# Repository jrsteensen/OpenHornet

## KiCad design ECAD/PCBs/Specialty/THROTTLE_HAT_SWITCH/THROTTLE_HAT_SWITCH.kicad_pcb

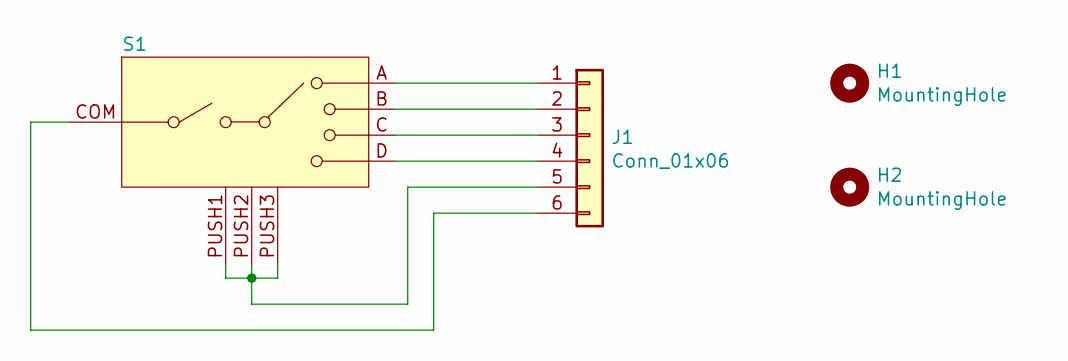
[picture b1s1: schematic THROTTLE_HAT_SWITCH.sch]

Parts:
H1, H2: MountingHole; MountingHole_3mm
J1: Conn_01x06; JST_PH_B6B-PH-K_1x06_P2.00mm_Vertical
S1: 8WayHat_CenterPush; RKJXM10

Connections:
unnamed: J1.1, S1.A
unnamed: J1.2, S1.B
unnamed: J1.3, S1.C
unnamed: J1.4, S1.D
unnamed: J1.5, S1.PUSH1, S1.PUSH2, S1.PUSH3
unnamed: J1.6, S1.COM

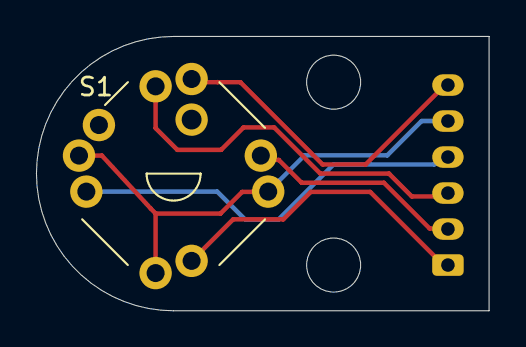
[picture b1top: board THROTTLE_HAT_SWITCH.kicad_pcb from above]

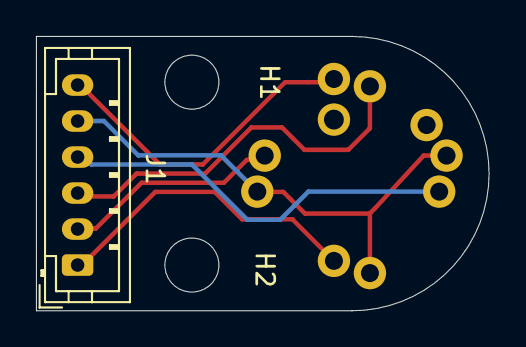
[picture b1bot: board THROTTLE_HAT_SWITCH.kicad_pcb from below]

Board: 2 copper layers, 25.1 x 15.2 mm, 4 parts (3 on the bottom side), 6 nets.

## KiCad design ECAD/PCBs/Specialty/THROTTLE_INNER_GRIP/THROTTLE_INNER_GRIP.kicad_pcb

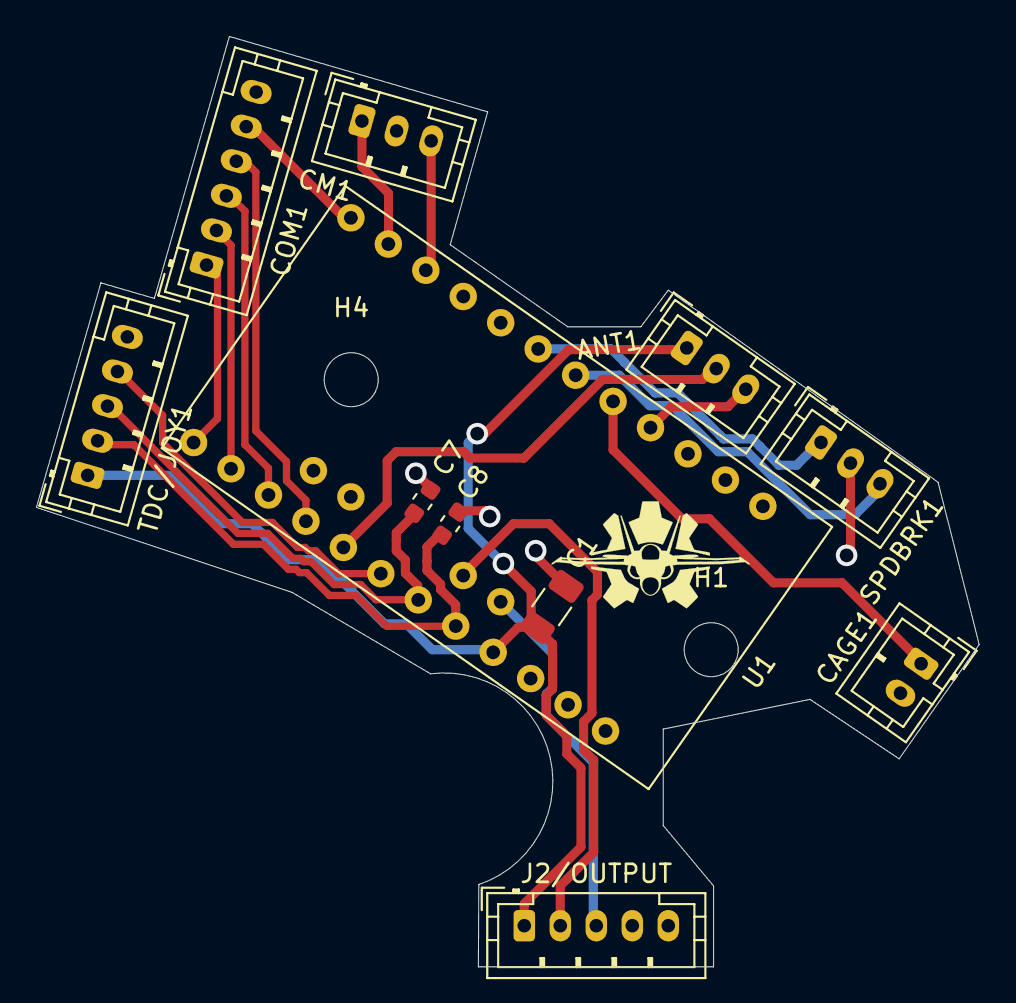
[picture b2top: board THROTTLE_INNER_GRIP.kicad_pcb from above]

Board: 2 copper layers, 52.4 x 51.7 mm, 13 parts (0 on the bottom side), 18 nets.

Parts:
ANT1: Conn_01x03; JST_PH_B3B-PH-K_1x03_P2.00mm_Vertical
C1: 10uF; C_1206_3216Metric
C7, C8: 0.1uF; C_0603_1608Metric
CAGE1: Conn_01x02; JST_PH_B2B-PH-K_1x02_P2.00mm_Vertical
CM1: Conn_01x03; JST_PH_B3B-PH-K_1x03_P2.00mm_Vertical
COM1: COMS; JST_PH_B6B-PH-K_1x06_P2.00mm_Vertical
H1, H4: MountingHole; MountingHole_3mm
J2/OUTPUT: BASE; JST_PH_B5B-PH-K_1x05_P2.00mm_Vertical
SPDBRK1: Conn_01x03; JST_PH_B3B-PH-K_1x03_P2.00mm_Vertical
TDC/JOY1: JOYSTICK; JST_PH_B5B-PH-K_1x05_P2.00mm_Vertical
U1: ProMini_NoProgrammingHeader; Arduino_Mini_Pro_No_Programming_Header

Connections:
/A: COM1.1, U1.13
/ANTENNA_ELEVATION: ANT1.2, U1.17
/B: COM1.2, U1.14
/C: COM1.3, U1.15
/CAGE-UNCAGE: CAGE1.1, U1.5
/COUNTERMEASURES_AFT: CM1.3, U1.10
/COUNTERMEASURES_FWD: CM1.1, U1.11
/D: COM1.4, U1.16
/I2C_DATA: J2/OUTPUT.2, U1.33
/I2C_SCK: J2/OUTPUT.3, U1.34
/JOY_SW: TDC/JOY1.4, U1.18
/JOY_X: C8.1, TDC/JOY1.2, U1.20
/JOY_Y: C7.1, TDC/JOY1.3, U1.19
/PUSH: COM1.5, U1.12
/SPEEDBREAK_EXTEND: SPDBRK1.1, U1.7
/SPEEDBREAK_RETRACT: SPDBRK1.3, U1.6
GND: ANT1.3, C1.2, C7.2, C8.2, CAGE1.2, CM1.2, COM1.6, J2/OUTPUT.5, SPDBRK1.2, TDC/JOY1.5, U1.4, U1.23
VCC: ANT1.1, C1.1, J2/OUTPUT.1, TDC/JOY1.1, U1.21

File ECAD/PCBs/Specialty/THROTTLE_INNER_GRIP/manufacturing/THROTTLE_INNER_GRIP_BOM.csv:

Comment,Designator,Footprint,LCSC
Conn_01x03,"ANT1,CM1,SP1",Connector_JST:JST_PH_B3B-PH-K_1x03_P2.00mm_Vertical,
10uF,C1,Capacitor_SMD:C_1206_3216Metric,C13585
0.1uF,"C7,C8",Capacitor_SMD:C_0603_1608Metric,C14663
Conn_01x02,CAGE1,Connector_JST:JST_PH_B2B-PH-K_1x02_P2.00mm_Vertical,
COMS,COM1,Connector_JST:JST_PH_B6B-PH-K_1x06_P2.00mm_Vertical,
MountingHole,"H1,H4",MountingHole:MountingHole_3mm,
BASE,J2,Connector_JST:JST_PH_B5B-PH-K_1x05_P2.00mm_Vertical,
JOYSTICK,JOY1,Connector_JST:JST_PH_B5B-PH-K_1x05_P2.00mm_Vertical,
ProMini_NoProgrammingHeader,U1,KiCAD_Libraries:Arduino_Mini_Pro_No_Programming_Header,

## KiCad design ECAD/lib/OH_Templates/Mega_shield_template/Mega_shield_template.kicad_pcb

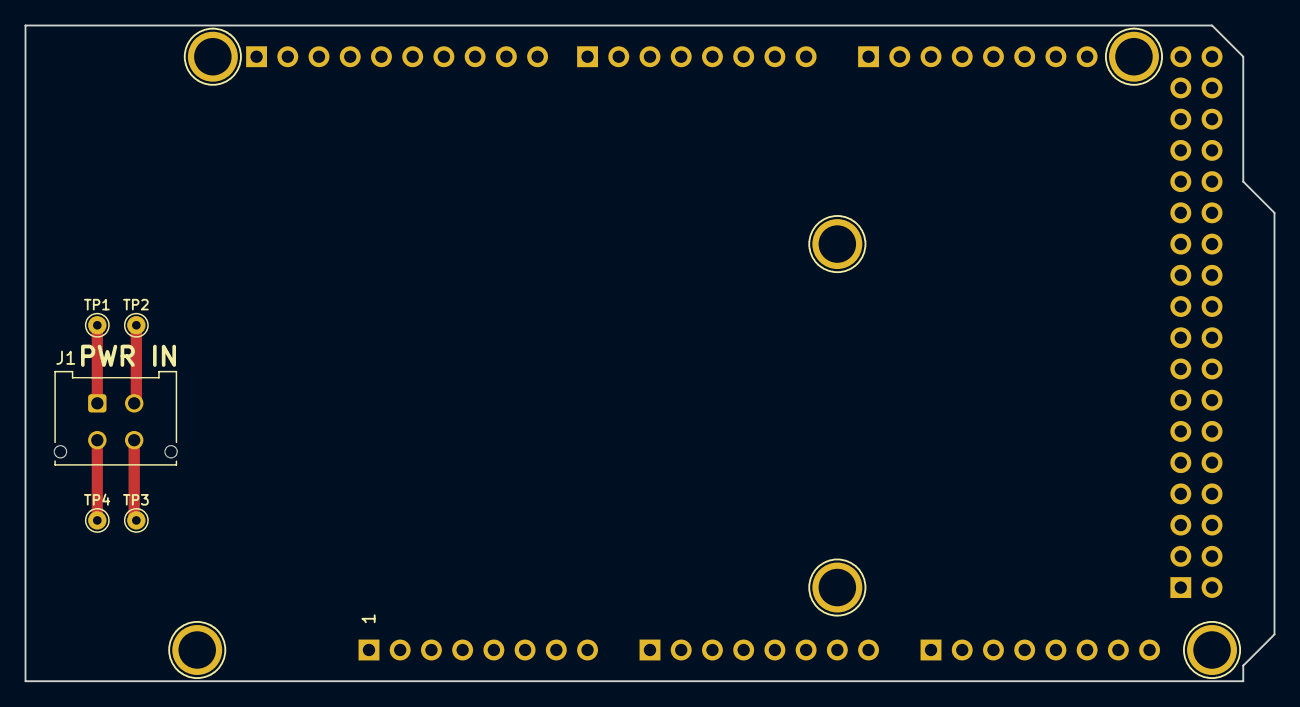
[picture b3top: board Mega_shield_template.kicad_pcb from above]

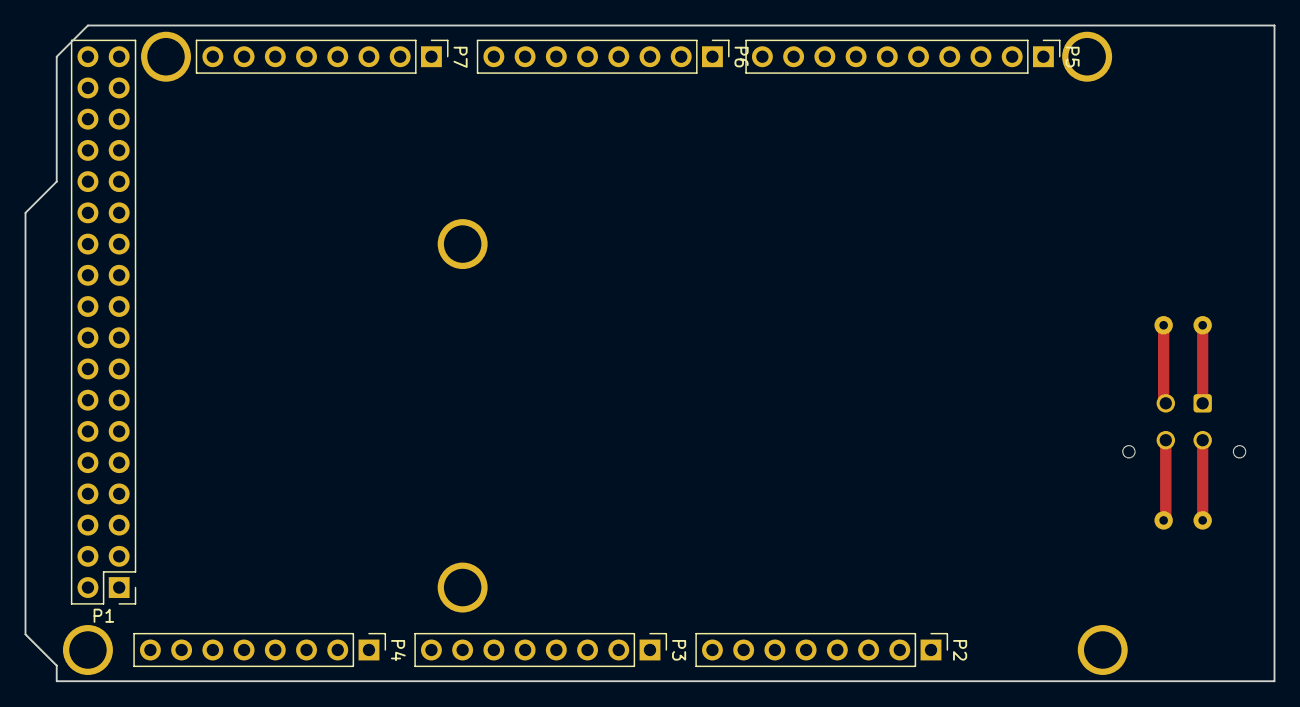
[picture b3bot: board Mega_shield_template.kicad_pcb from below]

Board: 2 copper layers, 101.6 x 53.3 mm, 18 parts (7 on the bottom side), 5 nets.

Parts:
J1: PWR IN; Molex_Micro-Fit_3.0_43045-0412_2x02_P3.00mm_Vertical
MK1, MK2, MK3, MK4, MK5, MK6: MH; Arduino_1pin
P1: Digital; PinHeader_2x18_P2.54mm_Vertical
P2: Power; PinHeader_1x08_P2.54mm_Vertical
P3, P4: Analog; PinHeader_1x08_P2.54mm_Vertical
P5: PWM; PinHeader_1x10_P2.54mm_Vertical
P6: PWM; PinHeader_1x08_P2.54mm_Vertical
P7: Communication; PinHeader_1x08_P2.54mm_Vertical
TP1: TP-12; TestPoint_THTPad_D1.5mm_Drill0.7mm
TP2: TP-5V; TestPoint_THTPad_D1.5mm_Drill0.7mm
TP3: TP-3.3V; TestPoint_THTPad_D1.5mm_Drill0.7mm
TP4: TP-GND; TestPoint_THTPad_D1.5mm_Drill0.7mm

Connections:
+5VD: P1.35, P1.36
/+3.3V_SUPPLY: J1.4, TP3.1
/+5V_SUPPLY: J1.2, TP2.1
/+12V_SUPPLY: J1.1, P2.8, TP1.1
GND: J1.3, P1.1, P1.2, P2.6, P2.7, P5.4, TP4.1

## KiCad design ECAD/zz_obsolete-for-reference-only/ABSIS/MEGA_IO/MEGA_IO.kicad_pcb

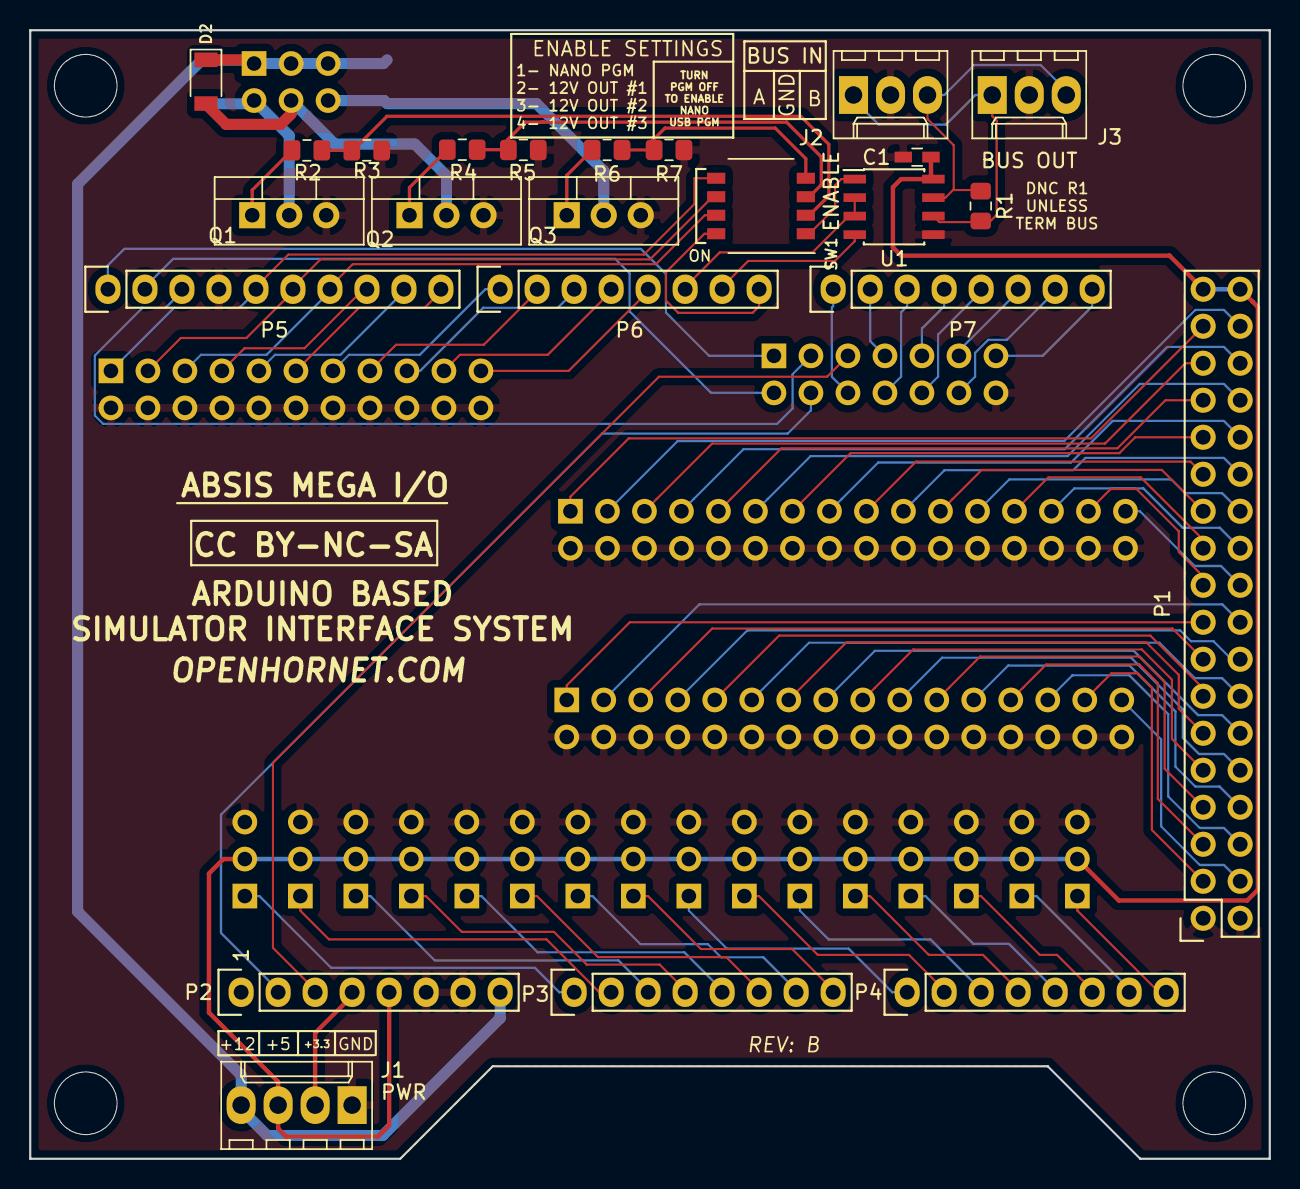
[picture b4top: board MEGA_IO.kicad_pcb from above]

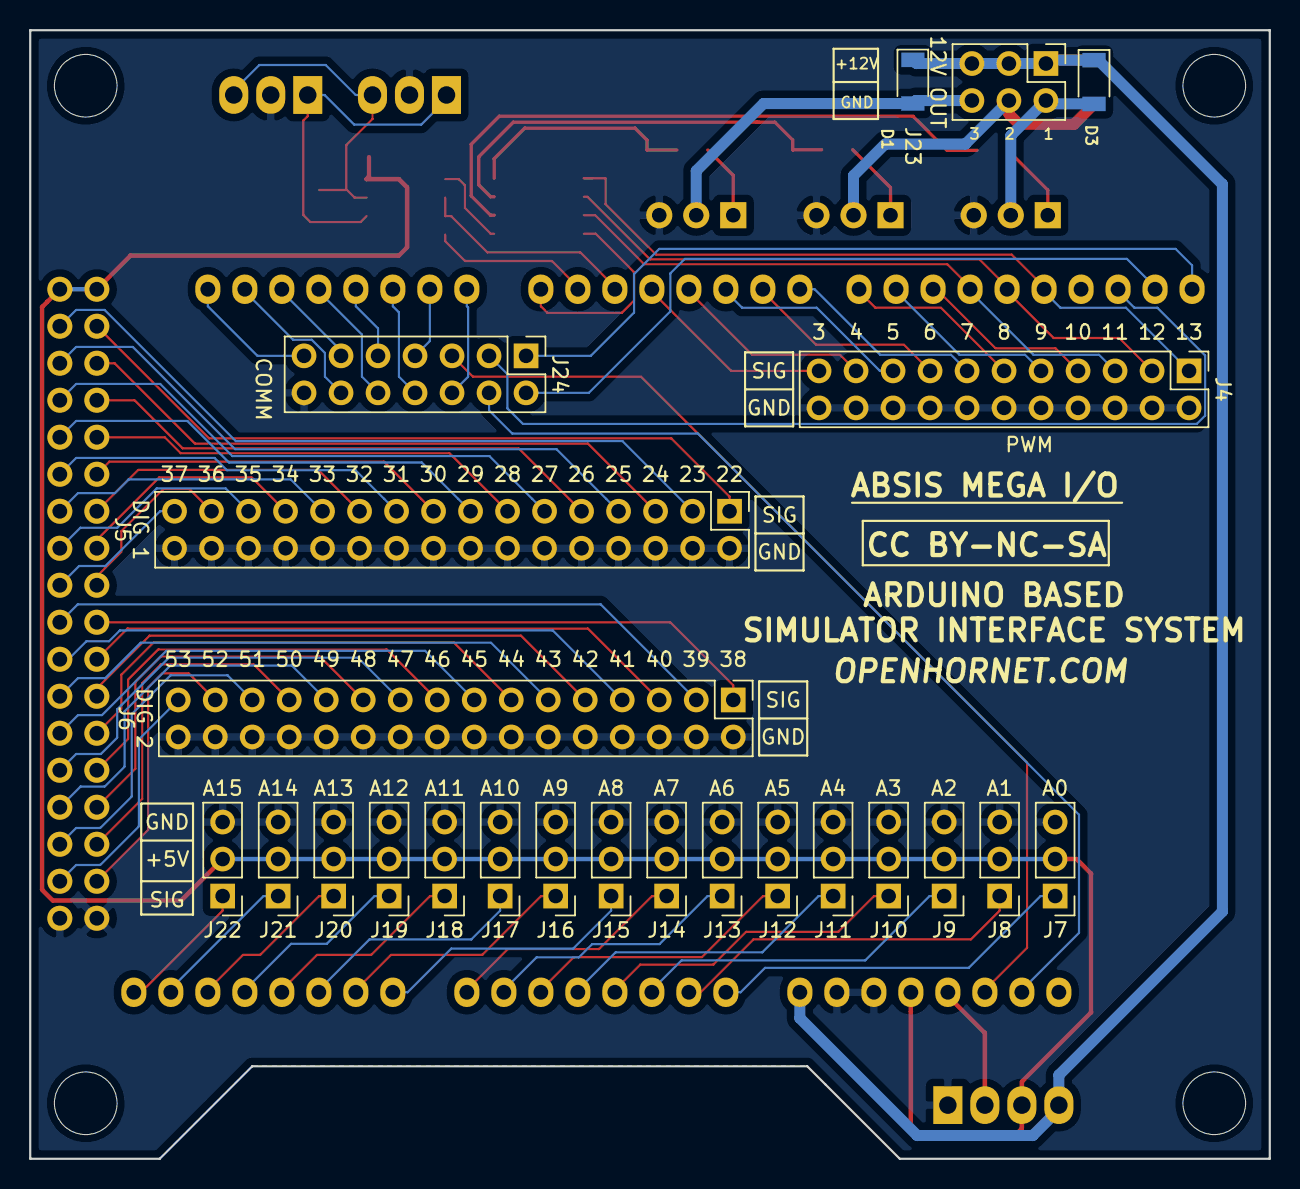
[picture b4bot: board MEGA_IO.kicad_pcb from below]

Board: 2 copper layers, 85.1 x 77.5 mm, 51 parts (23 on the bottom side), 91 nets.

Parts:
C1: 0.1uF; C_0603_HandSoldering
D1, D2, D3: 1N4001; D_1206
J1: PWR; Molex_KK-6410-04_04x2.54mm_Straight
J2: BUS IN; Molex_KK-6410-03_03x2.54mm_Straight
J3: BUS OUT; Molex_KK-6410-03_03x2.54mm_Straight
J4: PWM; Pin_Header_Straight_2x11_Pitch2.54mm
J5: DIG 1; Pin_Header_Straight_2x16_Pitch2.54mm
J6: DIG 2; Pin_Header_Straight_2x16_Pitch2.54mm
J7: A0; Pin_Header_Straight_1x03_Pitch2.54mm
J8: A1; Pin_Header_Straight_1x03_Pitch2.54mm
J9: A2; Pin_Header_Straight_1x03_Pitch2.54mm
J10: A3; Pin_Header_Straight_1x03_Pitch2.54mm
J11: A4; Pin_Header_Straight_1x03_Pitch2.54mm
J12: A5; Pin_Header_Straight_1x03_Pitch2.54mm
J13: A6; Pin_Header_Straight_1x03_Pitch2.54mm
J14: A7; Pin_Header_Straight_1x03_Pitch2.54mm
J15: A8; Pin_Header_Straight_1x03_Pitch2.54mm
J16: A9; Pin_Header_Straight_1x03_Pitch2.54mm
J17: A10; Pin_Header_Straight_1x03_Pitch2.54mm
J18: A11; Pin_Header_Straight_1x03_Pitch2.54mm
J19: A12; Pin_Header_Straight_1x03_Pitch2.54mm
J20: A13; Pin_Header_Straight_1x03_Pitch2.54mm
J21: A14; Pin_Header_Straight_1x03_Pitch2.54mm
J22: A15; Pin_Header_Straight_1x03_Pitch2.54mm
J23: 12V OUT; Pin_Header_Straight_2x03_Pitch2.54mm
J24: COMM; Pin_Header_Straight_2x07_Pitch2.54mm
MK1, MK2, MK3, MK4: Mounting_Hole; MountingHole_4.3mm_M4
P1: Digital; Socket_Strip_Arduino_2x18
P2: Power; Socket_Strip_Arduino_1x08
P3, P4: Analog; Socket_Strip_Arduino_1x08
P5: PWM; Socket_Strip_Arduino_1x10
P6: PWM; Socket_Strip_Arduino_1x08
P7: Communication; Socket_Strip_Arduino_1x08
Q1, Q3: Q_NMOS_DGS; TO-220-3_Vertical
Q2: Device:Q_NMOS_GDS; TO-220-3_Vertical
R1: 120; R_0805_2012Metric_Pad1.15x1.40mm_HandSolder
R2, R3, R4, R5, R6, R7: 1K; R_0805_2012Metric_Pad1.15x1.40mm_HandSolder
SW1: ENABLE; SW_DIP_x4_W6.15mm_Slide_Omron_A6H
U1: MAX487EESA; SOIC-8_3.9x4.9mm_Pitch1.27mm

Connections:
+3V3: J1.2, P2.4
+5V: C1.1, J1.3, J7.2, J8.2, J9.2, J10.2, J11.2, J12.2, J13.2, J14.2, J15.2, J16.2, J17.2, J18.2, J19.2, J20.2, J21.2, J22.2, P1.35, P1.36, P2.5, U1.8
+12V: D1.1, D2.1, D3.1, J1.4, J23.1, J23.3, J23.5, P2.8
/0(Rx0): P6.8, SW1.8
/1(Tx0): P6.7, U1.4
/2(**): P6.6, U1.2, U1.3
/3(**): J4.21, P6.5
/4(**): J4.19, P6.4
/5(**): J4.17, P6.3
/6(**): J4.15, P6.2
/7(**): J4.13, P6.1
/8(**): J4.11, P5.10
/9(**): J4.9, P5.9
/10(**): J4.7, P5.8
/11(**): J4.5, P5.7, SW1.7
/12(**): J4.3, P5.6, SW1.6
/13(**): J4.1, P5.5, SW1.5
/14(Tx3): J24.6, P7.1
/15(Rx3): J24.7, P7.2
/16(Tx2): J24.8, P7.3
/17(Rx2): J24.9, P7.4
/18(Tx1): J24.10, P7.5
/19(Rx1): J24.11, P7.6
/20(SDA): J24.12, P7.7
/21(SCL): J24.13, P7.8
/22: J5.1, P1.33
/23: J5.3, P1.34
/24: J5.5, P1.31
/25: J5.7, P1.32
/26: J5.9, P1.29
/27: J5.11, P1.30
/28: J5.13, P1.27
/29: J5.15, P1.28
/30: J5.17, P1.25
/31: J5.19, P1.26
/32: J5.21, P1.23
/33: J5.23, P1.24
/34: J5.25, P1.21
/35: J5.27, P1.22
/36: J5.29, P1.19
/37: J5.31, P1.20
/38: J6.1, P1.17
/39: J6.3, P1.18
/40: J6.5, P1.15
/41: J6.7, P1.16
/42: J6.9, P1.13
/43: J6.11, P1.14
/44: J6.13, P1.11
/45: J6.15, P1.12
/46: J6.17, P1.9
/47: J6.19, P1.10
/48: J6.21, P1.7
/49: J6.23, P1.8
/50(MISO): J6.25, P1.5
/51(MOSI): J6.27, P1.6
/52(SCK): J6.29, P1.3
/53(SS): J6.31, P1.4
/A0: J7.1, P3.1
/A1: J8.1, P3.2
/A2: J9.1, P3.3
/A3: J10.1, P3.4
/A4: J11.1, P3.5
/A5: J12.1, P3.6
/A6: J13.1, P3.7
/A7: J14.1, P3.8
/A8: J15.1, P4.1
/A9: J16.1, P4.2
/A10: J17.1, P4.3
/A11: J18.1, P4.4
/A12: J19.1, P4.5
/A13: J20.1, P4.6
/A14: J21.1, P4.7
/A15: J22.1, P4.8
/AREF: J24.3, P5.3
/IOREF: J24.4, P2.2
/RX_ENABLE: SW1.1, U1.1
/Reset: J24.5, P2.3
/SCL: J24.1, P5.1
/SDA: J24.2, P5.2
GND: C1.2, J1.1, J2.2, J3.2, J4.2, J4.4, J4.6, J4.8, J4.10, J4.12, J4.14, J4.16, J4.18, J4.20, J4.22, J5.2, J5.4, J5.6, J5.8, J5.10, J5.12, J5.14, J5.16, J5.18, J5.20, J5.22, J5.24, J5.26, J5.28, J5.30, J5.32, J6.2, J6.4, J6.6, J6.8, J6.10, J6.12, J6.14, J6.16, J6.18, J6.20, J6.22, J6.24, J6.26, J6.28, J6.30, J6.32, J7.3, J8.3, J9.3, J10.3, J11.3, J12.3, J13.3, J14.3, J15.3, J16.3, J17.3, J18.3, J19.3, J20.3, J21.3, J22.3, J24.14, P1.1, P1.2, P2.6, P2.7, P5.4, Q1.3, Q2.3, Q3.3, R3.1, R5.1, R7.1, U1.5
unnamed: D1.2, J23.6, Q3.2
unnamed: D2.2, J23.4, Q2.2
unnamed: D3.2, J23.2, Q1.2
unnamed: J2.1, J3.1, R1.2, U1.6
unnamed: J2.3, J3.3, R1.1, U1.7
unnamed: Q1.1, R2.2
unnamed: Q2.1, R4.2
unnamed: Q3.1, R6.2
unnamed: R2.1, R3.2, SW1.2
unnamed: R4.1, R5.2, SW1.3
unnamed: R6.1, R7.2, SW1.4

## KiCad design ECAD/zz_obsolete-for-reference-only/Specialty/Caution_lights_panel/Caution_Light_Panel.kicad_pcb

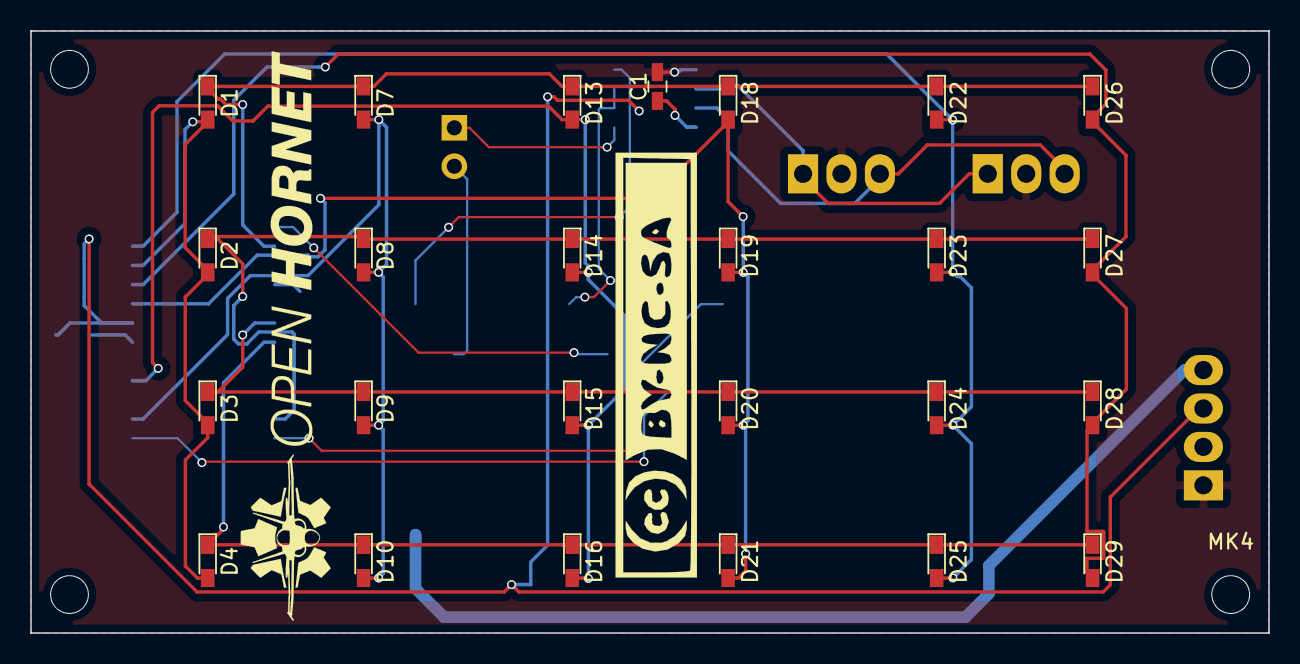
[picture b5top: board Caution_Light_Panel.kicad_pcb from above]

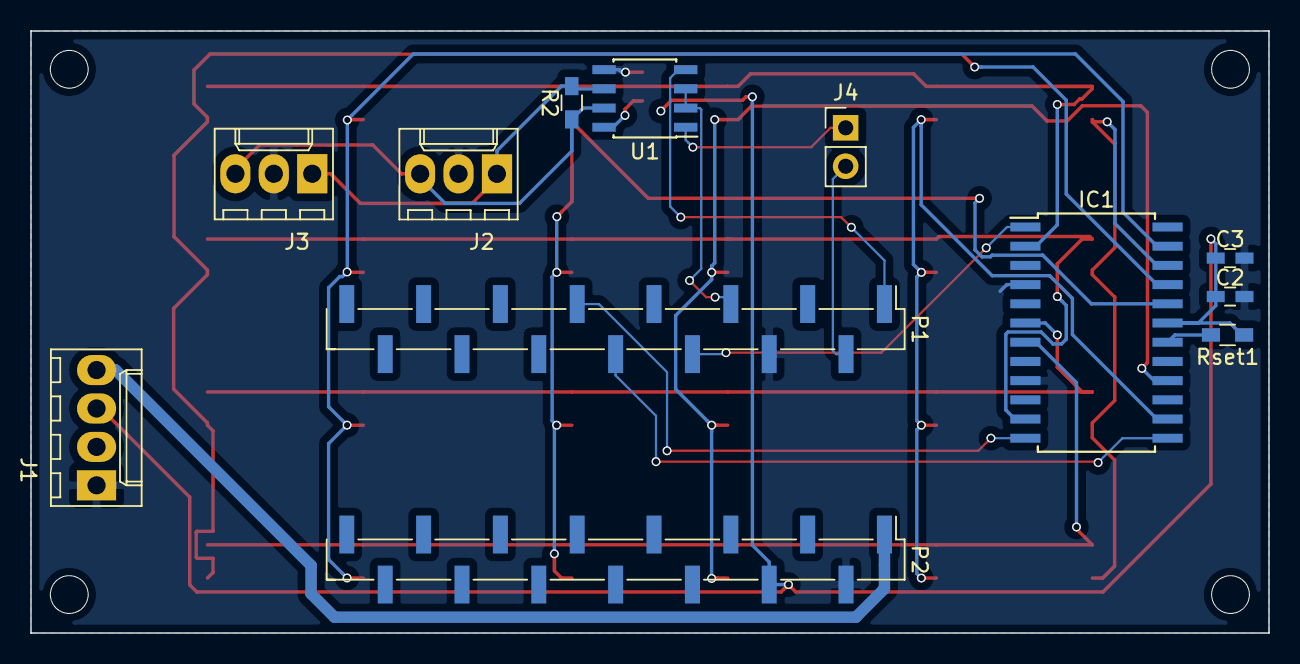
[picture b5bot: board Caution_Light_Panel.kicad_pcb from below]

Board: 2 copper layers, 81.9 x 39.8 mm, 41 parts (12 on the bottom side), 23 nets.

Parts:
C1: 0.1uF; C_0603_HandSoldering
C2: 100nF; C_0603_HandSoldering
C3: 47uF; C_0603_HandSoldering
D1: 0,0; LED_0603_HandSoldering
D2: 1,0; LED_0603_HandSoldering
D3: 2,0; LED_0603_HandSoldering
D4: 3,0; LED_0603_HandSoldering
D7: 0,1; LED_0603_HandSoldering
D8: 1,1; LED_0603_HandSoldering
D9: 2,1; LED_0603_HandSoldering
D10: 3,1; LED_0603_HandSoldering
D13: 0,2; LED_0603_HandSoldering
D14: 1,2; LED_0603_HandSoldering
D15: 2,2; LED_0603_HandSoldering
D16: 3,2; LED_0603_HandSoldering
D18: 0,3; LED_0603_HandSoldering
D19: 1.3; LED_0603_HandSoldering
D20: 2,3; LED_0603_HandSoldering
D21: 3,3; LED_0603_HandSoldering
D22: 0.4; LED_0603_HandSoldering
D23: 1.4; LED_0603_HandSoldering
D24: 2,4; LED_0603_HandSoldering
D25: 3,4; LED_0603_HandSoldering
D26: 0.5; LED_0603_HandSoldering
D27: 1.5; LED_0603_HandSoldering
D28: 2,5; LED_0603_HandSoldering
D29: 3,5; LED_0603_HandSoldering
IC1: MAX7219; SOIC-24W_7.5x15.4mm_Pitch1.27mm
J1: PWR; Molex_KK-6410-04_04x2.54mm_Straight
J2: BUS IN; Molex_KK-6410-03_03x2.54mm_Straight
J3: BUS OUT; Molex_KK-6410-03_03x2.54mm_Straight
J4: PGM ENBLE; Pin_Header_Straight_1x02_Pitch2.54mm
MK1, MK2, MK3, MK4: Mounting_Hole; MountingHole_2.5mm
P1: Digital; Pin_Header_Straight_1x15_Pitch2.54mm_SMD_Pin1Left
P2: Analog; Pin_Header_Straight_1x15_Pitch2.54mm_SMD_Pin1Left
R2: 120; R_0603_HandSoldering
Rset1: 30K; R_0603_HandSoldering
U1: MAX487EESA; SOIC-8_3.9x4.9mm_Pitch1.27mm

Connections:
+5V: C1.1, C2.1, C3.1, IC1.19, J1.3, P2.4, Rset1.1, U1.8
+12V: J1.4, P2.1
/0(Rx): J4.2, P1.2
/1(Tx): P1.1, U1.4
/2: P1.5, U1.2, U1.3
/3(**): IC1.1, P1.6
/5(**): IC1.13, P1.8
/6(**): IC1.12, P1.9
/Dig0: D1.1, D7.1, D13.1, D18.1, D22.1, D26.1, IC1.2
/Dig1: D2.1, D8.1, D14.1, D19.1, D23.1, D27.1, IC1.11
/Dig2: D3.1, D9.1, D15.1, D20.1, D24.1, D28.1, IC1.6
/Dig3: D4.1, D10.1, D16.1, D21.1, D25.1, D29.1, IC1.7
/RX_ENABLE: J4.1, U1.1
/SegA: D7.2, D8.2, D9.2, D10.2, IC1.14
/SegB: D13.2, D14.2, D15.2, D16.2, IC1.16
/SegC: D18.2, D19.2, D20.2, D21.2, IC1.20
/SegD: D22.2, D23.2, D24.2, D25.2, IC1.23
/SegDP: D1.2, D2.2, D3.2, D4.2, IC1.22
/SegE: D26.2, D27.2, D28.2, D29.2, IC1.21
GND: C1.2, C2.2, C3.2, IC1.4, IC1.9, J1.1, J2.2, J3.2, P1.4, P2.2, U1.5
unnamed: IC1.18, Rset1.2
unnamed: J2.1, J3.1, R2.2, U1.6
unnamed: J2.3, J3.3, R2.1, U1.7

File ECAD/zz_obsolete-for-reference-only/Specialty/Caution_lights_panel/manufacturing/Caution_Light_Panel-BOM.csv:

"Id";"Designator";"Package";"Quantity";"Designation";"Supplier and ref";
1;"G***";"CC-BY-NC-SA-Small";1;"LOGO";;;
2;"G***";"OH_LOGO_37.7mm_5.9mm";1;"LOGO";;;
3;"C1";"C_0603_HandSoldering";1;"0.1uF";;;
4;"C2";"C_0603_HandSoldering";1;"100nF";;;
5;"C3";"C_0603_HandSoldering";1;"47uF";;;
6;"D1";"LED_0603_HandSoldering";1;"0,0";;;
7;"D2";"LED_0603_HandSoldering";1;"1,0";;;
8;"D3";"LED_0603_HandSoldering";1;"2,0";;;
9;"D4";"LED_0603_HandSoldering";1;"3,0";;;
10;"D7";"LED_0603_HandSoldering";1;"0,1";;;
11;"D8";"LED_0603_HandSoldering";1;"1,1";;;
12;"D9";"LED_0603_HandSoldering";1;"2,1";;;
13;"D10";"LED_0603_HandSoldering";1;"3,1";;;
14;"D13";"LED_0603_HandSoldering";1;"0,2";;;
15;"D14";"LED_0603_HandSoldering";1;"1,2";;;
16;"D15";"LED_0603_HandSoldering";1;"2,2";;;
17;"D16";"LED_0603_HandSoldering";1;"3,2";;;
18;"D18";"LED_0603_HandSoldering";1;"0,3";;;
19;"D19";"LED_0603_HandSoldering";1;"1.3";;;
20;"D20";"LED_0603_HandSoldering";1;"2,3";;;
21;"D21";"LED_0603_HandSoldering";1;"3,3";;;
22;"D22";"LED_0603_HandSoldering";1;"0.4";;;
23;"D23";"LED_0603_HandSoldering";1;"1.4";;;
24;"D24";"LED_0603_HandSoldering";1;"2,4";;;
25;"D25";"LED_0603_HandSoldering";1;"3,4";;;
26;"D26";"LED_0603_HandSoldering";1;"0.5";;;
27;"D27";"LED_0603_HandSoldering";1;"1.5";;;
28;"D28";"LED_0603_HandSoldering";1;"2,5";;;
29;"D29";"LED_0603_HandSoldering";1;"3,5";;;
30;"IC1";"SOIC-24W_7.5x15.4mm_Pitch1.27mm";1;"MAX7219";;;
31;"J1";"Molex_KK-6410-04_04x2.54mm_Straight";1;"PWR";;;
32;"J2";"Molex_KK-6410-03_03x2.54mm_Straight";1;"BUS IN";;;
33;"J3";"Molex_KK-6410-03_03x2.54mm_Straight";1;"BUS OUT";;;
34;"J4";"Pin_Header_Straight_1x02_Pitch2.54mm";1;"PGM ENBLE";;;
35;"MK1,MK2,MK3,MK4";"MountingHole_2.5mm";4;"Mounting_Hole";;;
36;"P1";"Pin_Header_Straight_1x15_Pitch2.54mm_SMD_Pin1Left";1;"Digital";;;
37;"P2";"Pin_Header_Straight_1x15_Pitch2.54mm_SMD_Pin1Left";1;"Analog";;;
38;"R2";"R_0603_HandSoldering";1;"120";;;
39;"Rset1";"R_0603_HandSoldering";1;"30K";;;
40;"U1";"SOIC-8_3.9x4.9mm_Pitch1.27mm";1;"MAX487EESA";;;
